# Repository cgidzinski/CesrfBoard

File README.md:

# CesrfBoard
Cesrf Board and Schematic Repo
Using Eagle 7.6.0

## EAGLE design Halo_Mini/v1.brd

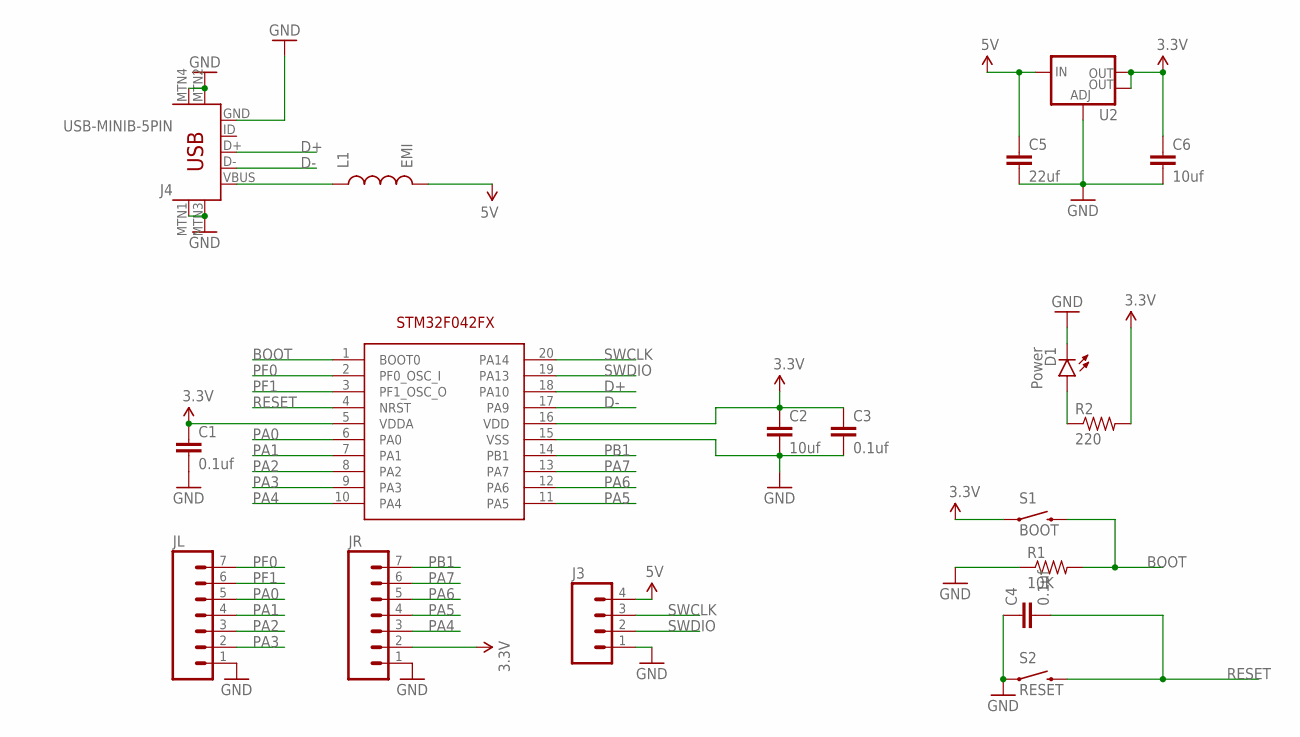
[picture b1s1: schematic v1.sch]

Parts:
C1, C3, C4: 0.1uf; 0805
C2, C6: 10uf; 0805
C5: 22uf; 0805
D1: Power; LED-1206
J3: M04NO_SILK_ALL_ROUND; 1X04_NO_SILK_ALL_ROUND
J4: USB-MINIB-5PIN; USB-MINIB
JL: M07NO_SILK; 1X07_NO_SILK
JR: M07NO_SILK; 1X07_NO_SILK
L1: EMI; 0805
R1: 10K; 0805
R2: 220; 0805
S1: BOOT; TACTILE-SWITCH-1101NE
S2: RESET; TACTILE-SWITCH-1101NE
U1: STM32F042FX; TSSOP20
U2: V_REG_LM1117SOT223; SOT223

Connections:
3.3V: C1.1, C2.1, C3.1, C6.1, JR.2, R2.2, S1.1, U1.5 (VDDA), U1.16 (VDD), U2.2 (OUT), U2.4 (OUT)
5V: C5.1, J3.4, L1.2, U2.3 (IN)
BOOT: R1.2, S1.2, U1.1 (BOOT0)
D+: J4.D+, U1.18 (PA10)
D-: J4.D-, U1.17 (PA9)
GND: C1.2, C2.2, C3.2, C4.1, C5.2, C6.2, D1.C, J3.1, J4.GND, J4.MTN1 (MTN2), J4.MTN2 (MTN3), J4.MTN3 (MTN1), J4.MTN4, JL.1, JR.1, R1.1, S2.1, U1.15 (VSS), U2.1 (ADJ)
unnamed: D1.A, R2.1
unnamed: J4.VBUS, L1.1
PA0: JL.5, U1.6 (PA0)
PA1: JL.4, U1.7 (PA1)
PA2: JL.3, U1.8 (PA2)
PA3: JL.2, U1.9 (PA3)
PA4: JR.3, U1.10 (PA4)
PA5: JR.4, U1.11 (PA5)
PA6: JR.5, U1.12 (PA6)
PA7: JR.6, U1.13 (PA7)
PB1: JR.7, U1.14 (PB1)
PF0: JL.7, U1.2 (PF0_OSC_I)
PF1: JL.6, U1.3 (PF1_OSC_O)
RESET: C4.2, S2.2, U1.4 (NRST)
SWCLK: J3.3, U1.20 (PA14)
SWDIO: J3.2, U1.19 (PA13)

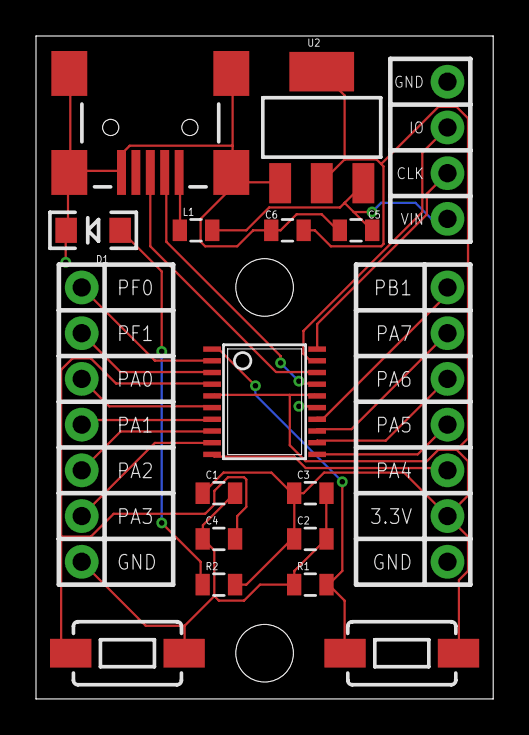
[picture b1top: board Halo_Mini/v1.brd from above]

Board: 2 copper layers, 25.4 x 36.8 mm, 18 parts (0 on the bottom side), 22 nets.

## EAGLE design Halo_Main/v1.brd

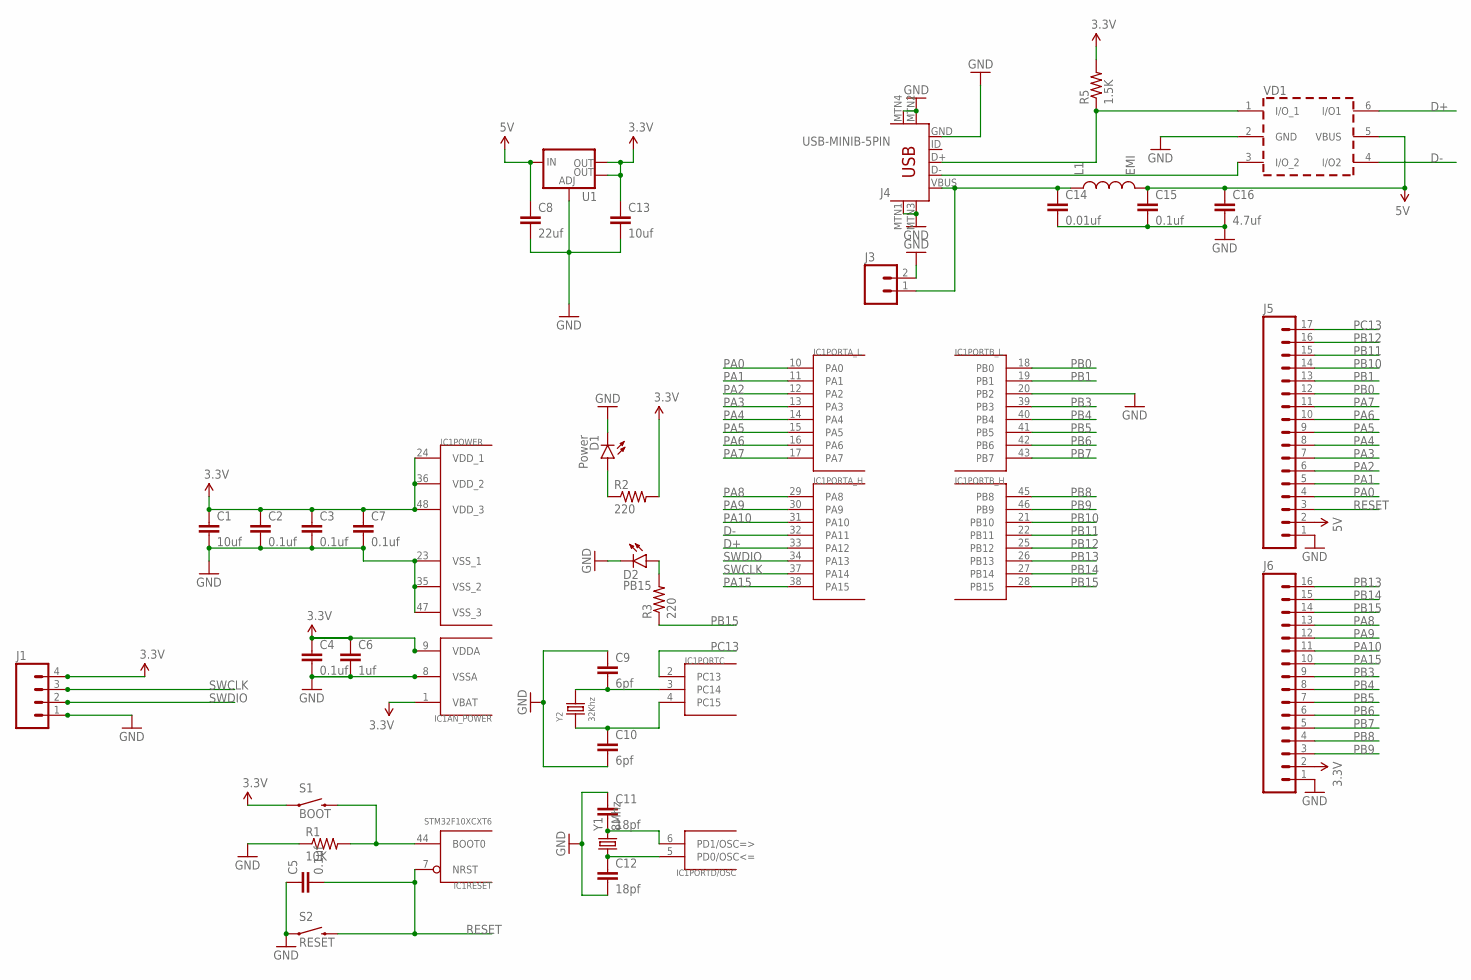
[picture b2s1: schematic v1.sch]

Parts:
C1, C13: 10uf; 0805
C2, C3, C4, C5, C7, C15: 0.1uf; 0805
C6: 1uf; 0805
C8: 22uf; 0805
C9, C10: 6pf; 0805
C11, C12: 18pf; 0805
C14: 0.01uf; 0805
C16: 4.7uf; 0805
D1: Power; LED-1206
D2: PB15; LED-1206
IC1: STM32F10XCXT6; TQFP48
J1: M04NO_SILK_ALL_ROUND; 1X04_NO_SILK_ALL_ROUND
J3: M021X02_NO_SILK; 1X02_NO_SILK
J4: USB-MINIB-5PIN; USB-MINIB
J5: M17NOSILK; 1X17_NO_SILK
J6: M161X16_NO_SILK; 1X16_NO_SILK
L1: EMI; 0805
R1: 10K; 0805
R2, R3: 220; 0805
R5: 1.5K; 0805
S1: BOOT; TACTILE-SWITCH-1101NE
S2: RESET; TACTILE-SWITCH-1101NE
U1: V_REG_LM1117SOT223; SOT223
VD1: USBLC6-2SC6; SOT-23-6L
Y1: 8Mhz; CRYSTAL-SMD-5X3
Y2: 32Khz; X2-SMD-3.2X1.5X0.55MM

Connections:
3.3V: C1.1, C2.1, C3.1, C4.1, C6.1, C7.1, C13.1, IC1.1 (VBAT), IC1.9 (VDDA), IC1.24 (VDD_1), IC1.36 (VDD_2), IC1.48 (VDD_3), J1.4, J6.2, R2.2, R5.2, S1.1, U1.2 (OUT), U1.4 (OUT)
5V: C8.1, C15.1, C16.1, J5.2, L1.2, U1.3 (IN), VD1.5 (VBUS)
D+: IC1.33 (PA12), VD1.6 (I/O1)
D-: IC1.32 (PA11), VD1.4 (I/O2)
GND: C1.2, C2.2, C3.2, C4.2, C5.1, C6.2, C7.2, C8.2, C9.1, C10.2, C11.1, C12.2, C13.2, C14.2, C15.2, C16.2, D1.C, D2.C, IC1.8 (VSSA), IC1.20 (PB2), IC1.23 (VSS_1), IC1.35 (VSS_2), IC1.47 (VSS_3), J1.1, J3.2, J4.GND, J4.MTN1 (MTN2), J4.MTN2 (MTN3), J4.MTN3 (MTN1), J4.MTN4, J5.1, J6.1, R1.1, S2.1, U1.1 (ADJ), VD1.2 (GND)
unnamed: D1.A, R2.1
unnamed: IC1.44 (BOOT0), R1.2, S1.2
unnamed: C11.2, IC1.6 (PD1/OSC=>), Y1.3 (2)
unnamed: C12.1, IC1.5 (PD0/OSC<=), Y1.1
unnamed: C9.2, IC1.3 (PC14), Y2.2
unnamed: D2.A, R3.2
unnamed: C10.1, IC1.4 (PC15), Y2.1
unnamed: C14.1, J3.1, J4.VBUS, L1.1
unnamed: J4.D+, R5.1, VD1.1 (I/O_1)
unnamed: J4.D-, VD1.3 (I/O_2)
PA0: IC1.10 (PA0), J5.4
PA1: IC1.11 (PA1), J5.5
PA2: IC1.12 (PA2), J5.6
PA3: IC1.13 (PA3), J5.7
PA4: IC1.14 (PA4), J5.8
PA5: IC1.15 (PA5), J5.9
PA6: IC1.16 (PA6), J5.10
PA7: IC1.17 (PA7), J5.11
PA8: IC1.29 (PA8), J6.13
PA9: IC1.30 (PA9), J6.12
PA10: IC1.31 (PA10), J6.11
PA15: IC1.38 (PA15), J6.10
PB0: IC1.18 (PB0), J5.12
PB1: IC1.19 (PB1), J5.13
PB3: IC1.39 (PB3), J6.9
PB4: IC1.40 (PB4), J6.8
PB5: IC1.41 (PB5), J6.7
PB6: IC1.42 (PB6), J6.6
PB7: IC1.43 (PB7), J6.5
PB8: IC1.45 (PB8), J6.4
PB9: IC1.46 (PB9), J6.3
PB10: IC1.21 (PB10), J5.14
PB11: IC1.22 (PB11), J5.15
PB12: IC1.25 (PB12), J5.16
PB13: IC1.26 (PB13), J6.16
PB14: IC1.27 (PB14), J6.15
PB15: IC1.28 (PB15), J6.14, R3.1
PC13: IC1.2 (PC13), J5.17
RESET: C5.2, IC1.7 (NRST), J5.3, S2.2
SWCLK: IC1.37 (PA14), J1.3
SWDIO: IC1.34 (PA13), J1.2

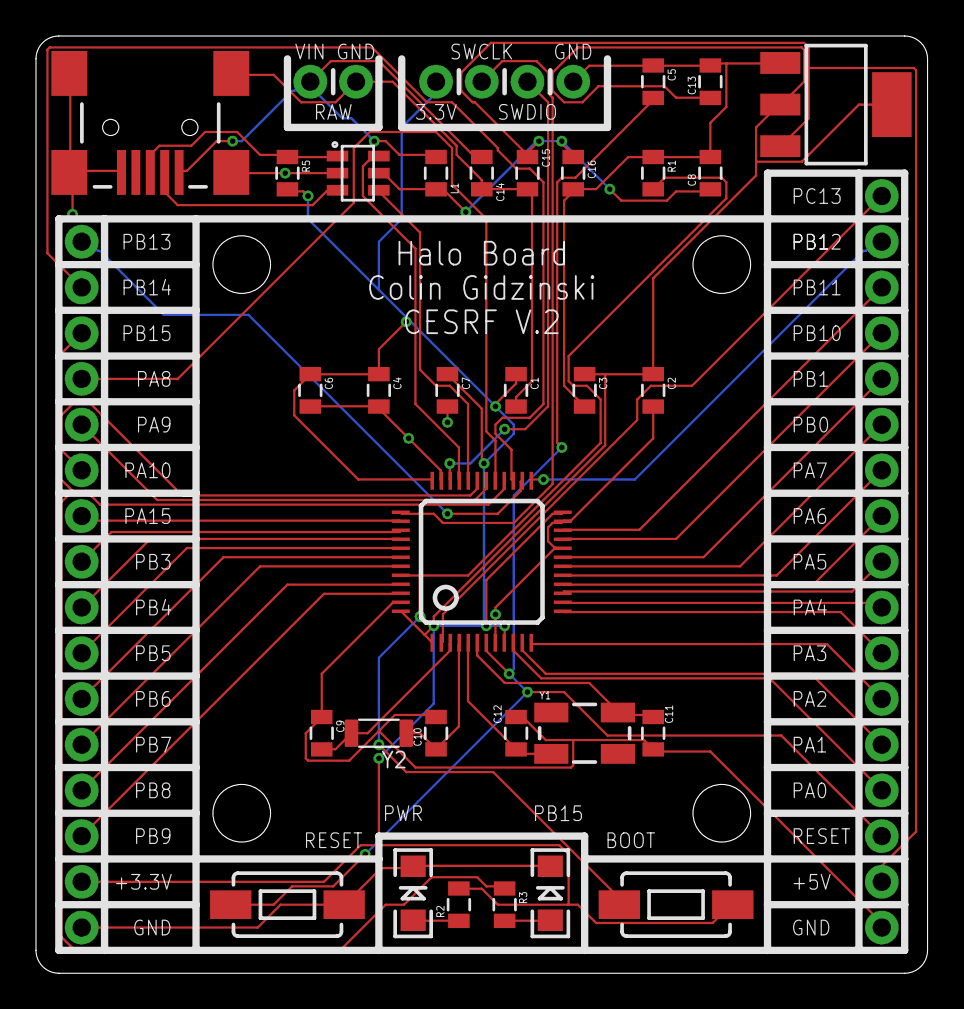
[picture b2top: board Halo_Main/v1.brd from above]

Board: 2 copper layers, 49.5 x 52.1 mm, 35 parts (0 on the bottom side), 46 nets.

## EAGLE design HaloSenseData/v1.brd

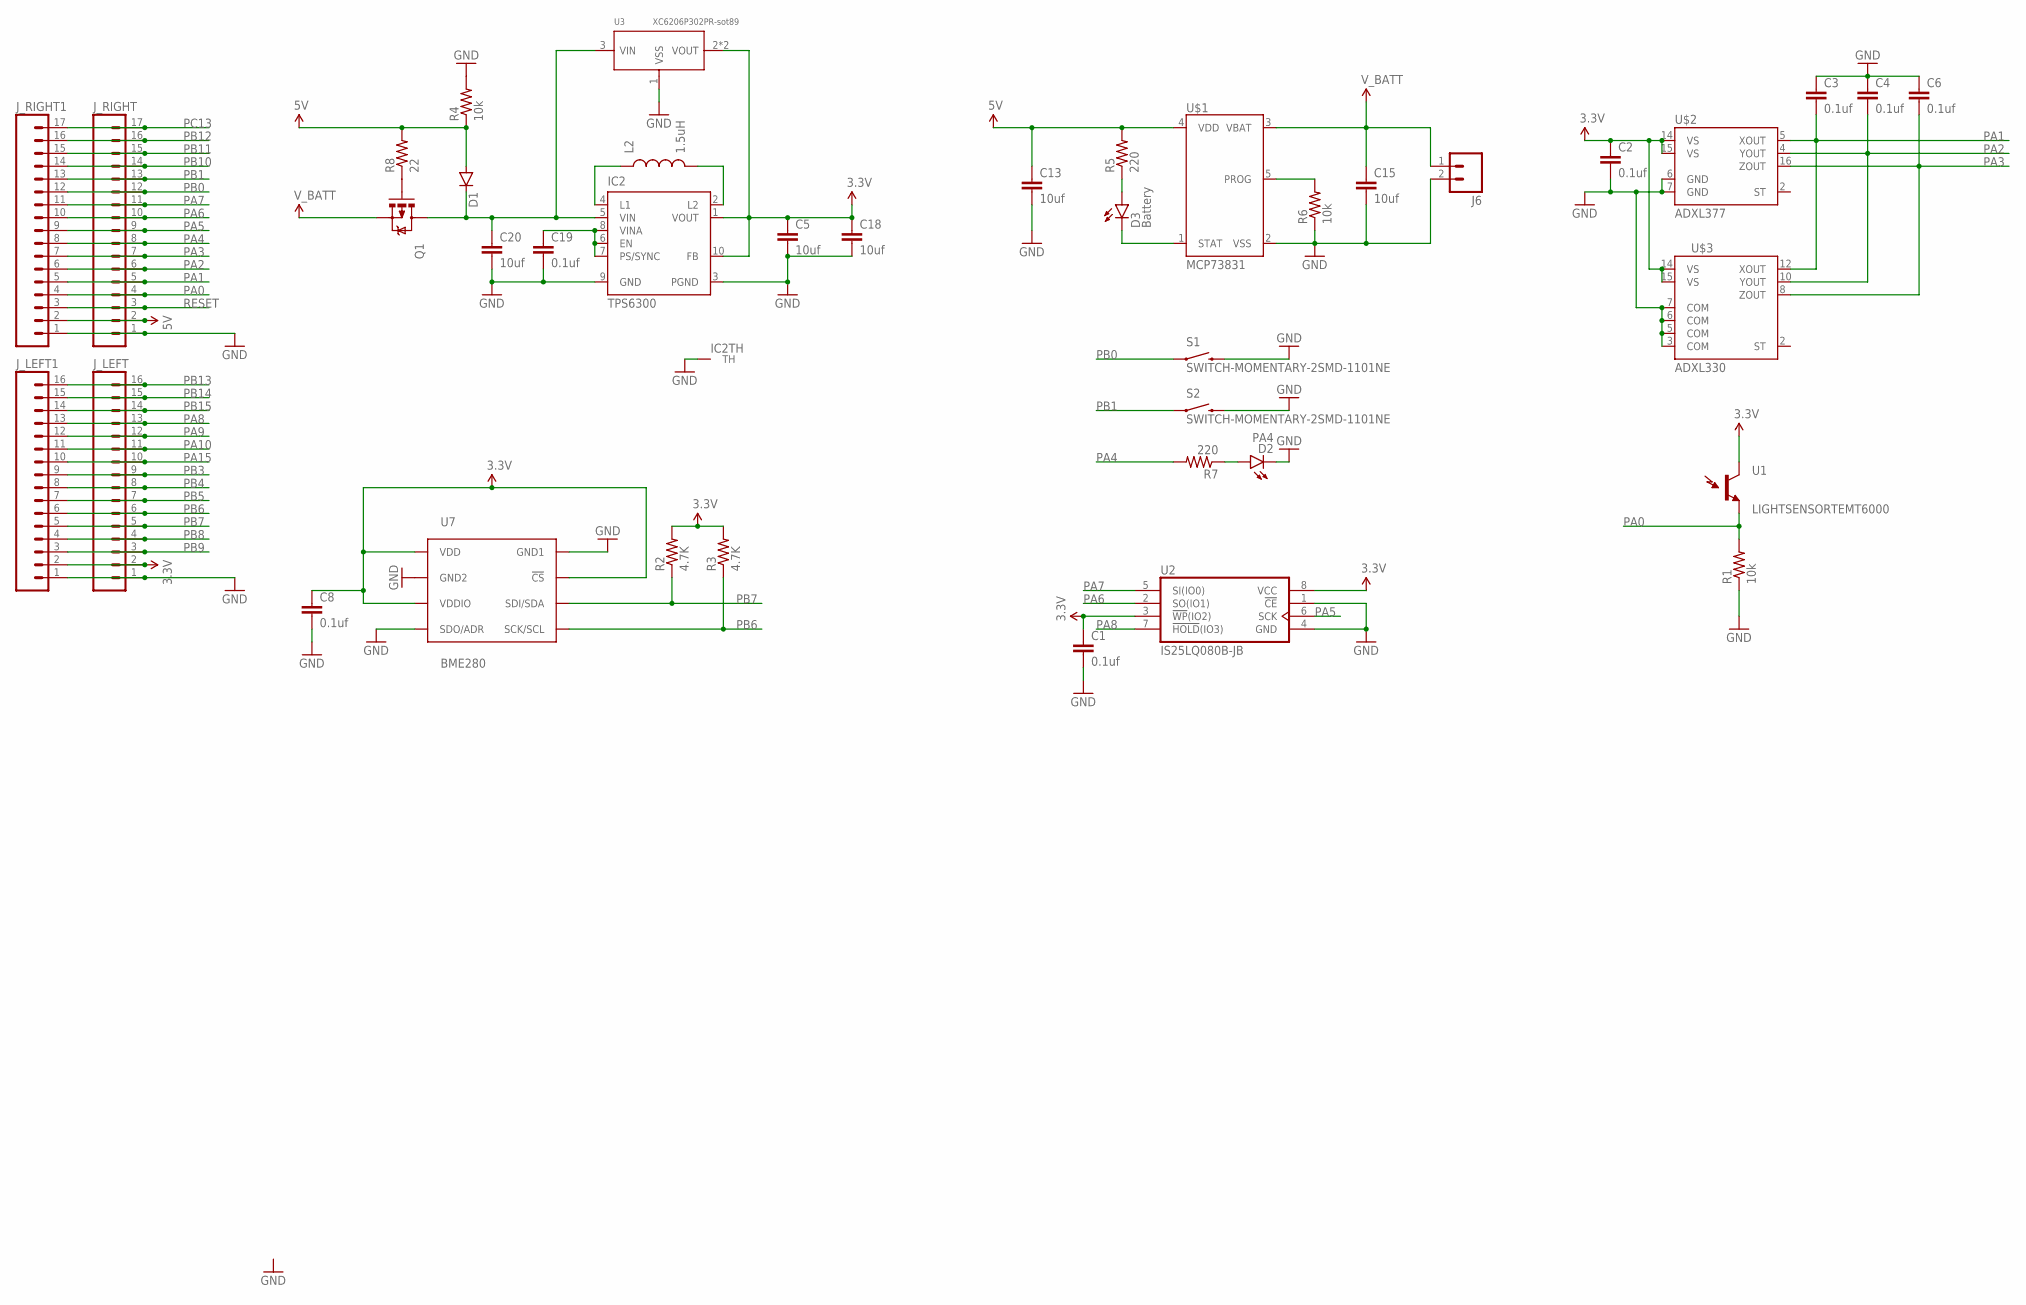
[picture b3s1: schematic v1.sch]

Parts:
C1, C2, C3, C4, C6, C8, C19: 0.1uf; 0805
C5, C13, C15, C18, C20: 10uf; 0805
D1: DIODESOD123; SOD-123
D2: PA4; LED-1206
D3: Battery; LED-1206
IC2: TPS6300; DRC-S-PVSON-N10
J6: M021X02_NO_SILK; 1X02_NO_SILK
J_LEFT, J_LEFT1: M161X16_NO_SILK; 1X16_NO_SILK
J_RIGHT, J_RIGHT1: M17NOSILK; 1X17_NO_SILK
L2: 1.5uH; SRN6045
Q1: MOSFET-PCHANNEL; SOT23-3
R1, R4, R6: 10k; 0805
R2, R3: 4.7K; 0805
R5, R7: 220; 0805
R8: 22; 0805
S1, S2: SWITCH-MOMENTARY-2SMD-1101NE; TACTILE-SWITCH-1101NE
U1: LIGHTSENSORTEMT6000; TEMT6000-SEN
U2: IS25LQ080B-JB; SO08-JB
U3: XC6206P302PR-sot89; SOT-89
U7: BME280; BME280_LGA
U$1: MCP73831; SOT23-5
U$2: ADXL377; LFCSP_LQ-16
U$3: ADXL330; LFCSP-16

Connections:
3.3V: C1.1, C2.1, C5.1, C8.1, C18.1, IC2.1 (VOUT), IC2.10 (FB), J_LEFT.2, J_LEFT1.2, R2.2, R3.2, U1.COLLECTOR (C1), U2.3 (!WP!(IO2)), U2.8 (VCC), U3.2 (VOUT), U3.4 (VOUT), U7.P$2 (!CS), U7.P$6 (VDDIO), U7.P$8 (VDD), U$2.14 (VS), U$2.15 (VS), U$3.14 (VS), U$3.15 (VS)
5V: C13.1, D1.A, J_RIGHT.2, J_RIGHT1.2, R4.1, R5.2, R8.2, U$1.4 (VDD)
GND: C1.2, C2.2, C3.1, C4.1, C5.2, C6.1, C8.2, C13.2, C15.2, C18.2, C19.2, C20.2, D2.C, IC2.3 (PGND), IC2.9 (GND), IC2.TH, J6.2, J_LEFT.1, J_LEFT1.1, J_RIGHT.1, J_RIGHT1.1, R1.1, R4.2, R6.1, S1.2, S2.2, U2.1 (!CE!), U2.4 (GND), U3.1 (VSS), U7.P$1 (GND1), U7.P$5 (SDO/ADR), U7.P$7 (GND2), U$1.2 (VSS), U$2.6 (GND), U$2.7 (GND), U$3.3 (COM), U$3.5 (COM), U$3.6 (COM), U$3.7 (COM)
unnamed: IC2.4 (L1), L2.1
unnamed: IC2.2 (L2), L2.2
unnamed: C20.1, D1.C, IC2.5 (VIN), Q1.3 (D), U3.3 (VIN)
unnamed: D2.A, R7.1
unnamed: Q1.1 (G), R8.1
unnamed: D3.A, R5.1
unnamed: C19.1, IC2.6 (EN), IC2.7 (PS/SYNC), IC2.8 (VINA)
unnamed: D3.C, U$1.1 (STAT)
unnamed: R6.2, U$1.5 (PROG)
PA0: J_RIGHT.4, J_RIGHT1.4, R1.2, U1.EMITTER (E1)
PA1: C3.2, J_RIGHT.5, J_RIGHT1.5, U$2.5 (XOUT), U$3.12 (XOUT)
PA2: C4.2, J_RIGHT.6, J_RIGHT1.6, U$2.4 (YOUT), U$3.10 (YOUT)
PA3: C6.2, J_RIGHT.7, J_RIGHT1.7, U$2.16 (ZOUT), U$3.8 (ZOUT)
PA4: J_RIGHT.8, J_RIGHT1.8, R7.2
PA5: J_RIGHT.9, J_RIGHT1.9, U2.6 (SCK)
PA6: J_RIGHT.10, J_RIGHT1.10, U2.2 (SO(IO1))
PA7: J_RIGHT.11, J_RIGHT1.11, U2.5 (SI(IO0))
PA8: J_LEFT.13, J_LEFT1.13, U2.7 (!HOLD!(IO3))
PA9: J_LEFT.12, J_LEFT1.12
PA10: J_LEFT.11, J_LEFT1.11
PA15: J_LEFT.10, J_LEFT1.10
PB0: J_RIGHT.12, J_RIGHT1.12, S1.1
PB1: J_RIGHT.13, J_RIGHT1.13, S2.1
PB3: J_LEFT.9, J_LEFT1.9
PB4: J_LEFT.8, J_LEFT1.8
PB5: J_LEFT.7, J_LEFT1.7
PB6: J_LEFT.6, J_LEFT1.6, R3.1, U7.P$4 (SCK/SCL)
PB7: J_LEFT.5, J_LEFT1.5, R2.1, U7.P$3 (SDI/SDA)
PB8: J_LEFT.4, J_LEFT1.4
PB9: J_LEFT.3, J_LEFT1.3
PB10: J_RIGHT.14, J_RIGHT1.14
PB11: J_RIGHT.15, J_RIGHT1.15
PB12: J_RIGHT.16, J_RIGHT1.16
PB13: J_LEFT.16, J_LEFT1.16
PB14: J_LEFT.15, J_LEFT1.15
PB15: J_LEFT.14, J_LEFT1.14
PC13: J_RIGHT.17, J_RIGHT1.17
RESET: J_RIGHT.3, J_RIGHT1.3
V_BATT: C15.1, J6.1, Q1.2 (S), U$1.3 (VBAT)

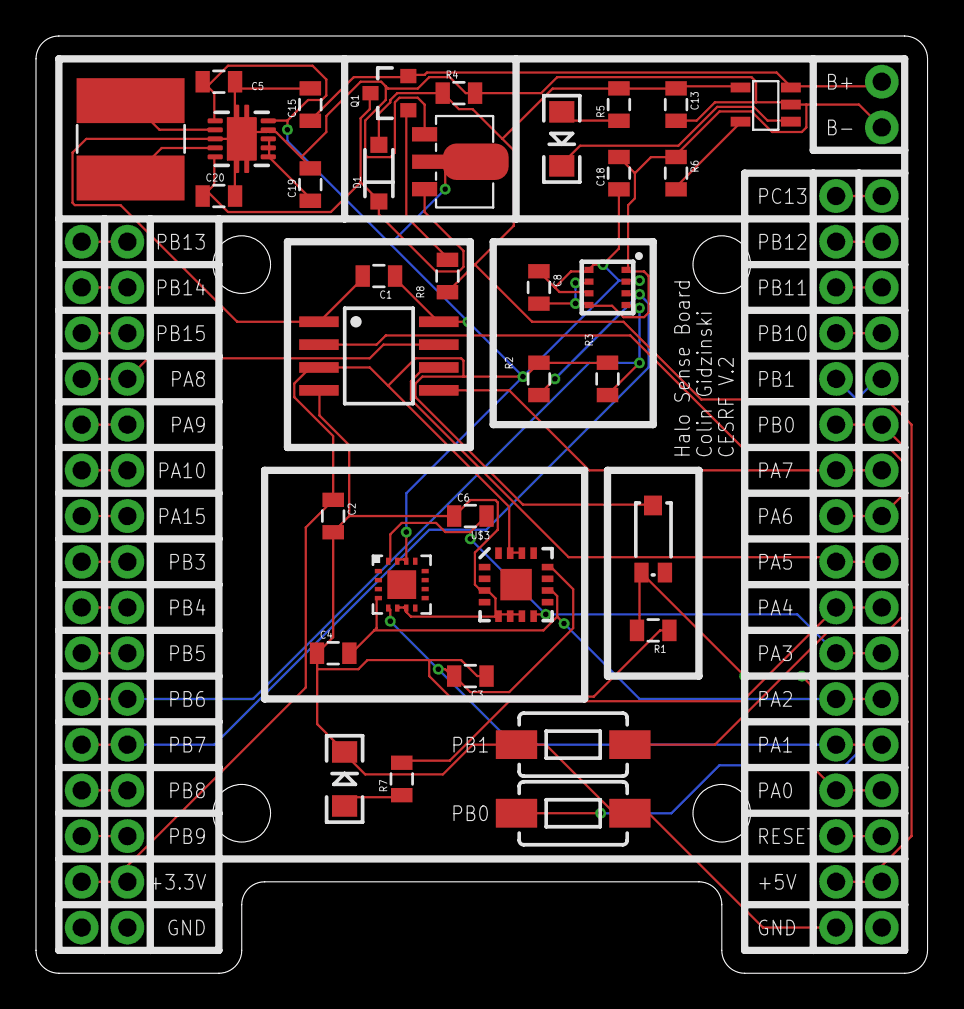
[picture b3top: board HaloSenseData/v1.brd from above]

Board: 2 copper layers, 49.5 x 52.1 mm, 40 parts (0 on the bottom side), 42 nets.

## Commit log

2016-09-26 :lollipop: Added .gitattributes & .gitignore files
2016-09-26 Base Files
2016-09-26 Purge
2016-09-26 Double Word
2016-09-26 Added Documentation

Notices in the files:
parts and their libraries:
SparkFun-Capacitors: Licensing: Creative Commons ShareAlike 4.0 International - https://creativecommons.org/licenses/by-sa/4.0
memory-issi: Copyright (C) 2015, Bob Starr
